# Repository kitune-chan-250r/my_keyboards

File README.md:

# my_keyboards

## первый
・34key,ortholinear,ISO Enter

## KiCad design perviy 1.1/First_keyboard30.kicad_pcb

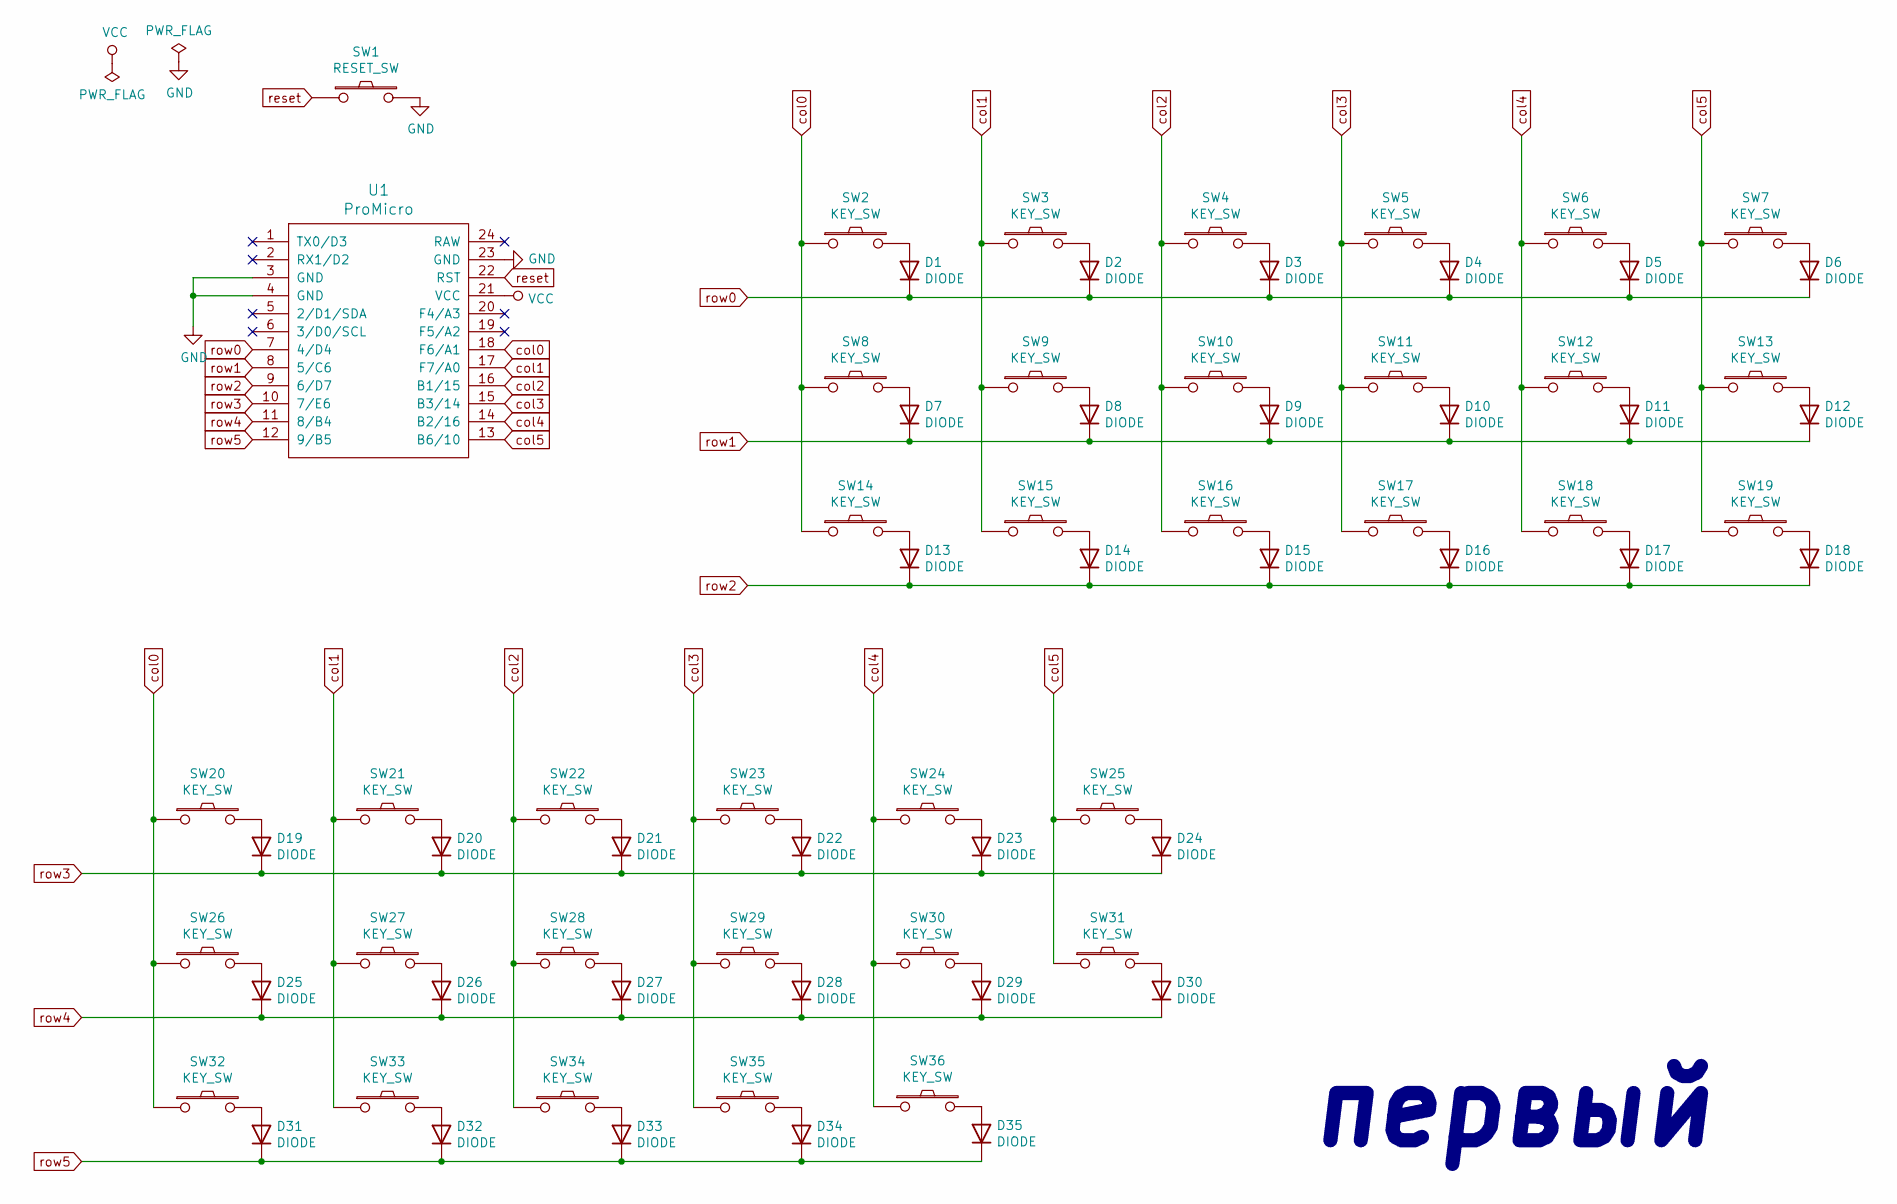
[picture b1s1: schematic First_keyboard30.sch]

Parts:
D1, D2, D3, D4, D5, D6, D7, D8, D9, D10, D11, D12, D13, D14, D15, D16, D17, D18, D19, D20, D21, D22, D23, D24, D25, D26, D27, D28, D29, D30, D31, D32, D33, D34, D35: DIODE; D3_TH_SMD
SW1: RESET_SW; ResetSW
SW2, SW3, SW4, SW5, SW6, SW7, SW8, SW9, SW10, SW11, SW12, SW13, SW16, SW17, SW18, SW19, SW20, SW21, SW22, SW23, SW24, SW25, SW26, SW27, SW28, SW29, SW30, SW31, SW32, SW33, SW34, SW35: KEY_SW; CherryMX_Hotswap
SW14, SW15: KEY_SW; CherryMX_1u
SW36: KEY_SW; MX-Alps-Choc-2U
U1: ProMicro; ProMicro_v3

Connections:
GND: SW1.2, U1.3 (GND), U1.4 (GND), U1.23 (GND)
unnamed: D1.1 (A), SW2.2
unnamed: D2.1 (A), SW3.2
unnamed: D3.1 (A), SW4.2
unnamed: D4.1 (A), SW5.2
unnamed: D5.1 (A), SW6.2
unnamed: D6.1 (A), SW7.2
unnamed: D7.1 (A), SW8.2
unnamed: D8.1 (A), SW9.2
unnamed: D9.1 (A), SW10.2
unnamed: D10.1 (A), SW11.2
unnamed: D11.1 (A), SW12.2
unnamed: D12.1 (A), SW13.2
unnamed: D13.1 (A), SW14.2
unnamed: D14.1 (A), SW15.2
unnamed: D15.1 (A), SW16.2
unnamed: D16.1 (A), SW17.2
unnamed: D17.1 (A), SW18.2
unnamed: D18.1 (A), SW19.2
unnamed: D19.1 (A), SW20.2
unnamed: D20.1 (A), SW21.2
unnamed: D21.1 (A), SW22.2
unnamed: D22.1 (A), SW23.2
unnamed: D23.1 (A), SW24.2
unnamed: D24.1 (A), SW25.2
unnamed: D25.1 (A), SW26.2
unnamed: D26.1 (A), SW27.2
unnamed: D27.1 (A), SW28.2
unnamed: D28.1 (A), SW29.2
unnamed: D29.1 (A), SW30.2
unnamed: D30.1 (A), SW31.2
unnamed: D31.1 (A), SW32.2
unnamed: D32.1 (A), SW33.2
unnamed: D33.1 (A), SW34.2
unnamed: D34.1 (A), SW35.2
unnamed: D35.1 (A), SW36.2
VCC: U1.21 (VCC)
col0: SW2.1, SW8.1, SW14.1, SW20.1, SW26.1, SW32.1, U1.18 (F6/A1)
col1: SW3.1, SW9.1, SW15.1, SW21.1, SW27.1, SW33.1, U1.17 (F7/A0)
col2: SW4.1, SW10.1, SW16.1, SW22.1, SW28.1, SW34.1, U1.16 (B1/15)
col3: SW5.1, SW11.1, SW17.1, SW23.1, SW29.1, SW35.1, U1.15 (B3/14)
col4: SW6.1, SW12.1, SW18.1, SW24.1, SW30.1, SW36.1, U1.14 (B2/16)
col5: SW7.1, SW13.1, SW19.1, SW25.1, SW31.1, U1.13 (B6/10)
reset: SW1.1, U1.22 (RST)
row0: D1.2 (K), D2.2 (K), D3.2 (K), D4.2 (K), D5.2 (K), D6.2 (K), U1.7 (4/D4)
row1: D7.2 (K), D8.2 (K), D9.2 (K), D10.2 (K), D11.2 (K), D12.2 (K), U1.8 (5/C6)
row2: D13.2 (K), D14.2 (K), D15.2 (K), D16.2 (K), D17.2 (K), D18.2 (K), U1.9 (6/D7)
row3: D19.2 (K), D20.2 (K), D21.2 (K), D22.2 (K), D23.2 (K), D24.2 (K), U1.10 (7/E6)
row4: D25.2 (K), D26.2 (K), D27.2 (K), D28.2 (K), D29.2 (K), D30.2 (K), U1.11 (8/B4)
row5: D31.2 (K), D32.2 (K), D33.2 (K), D34.2 (K), D35.2 (K), U1.12 (9/B5)

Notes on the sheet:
первый

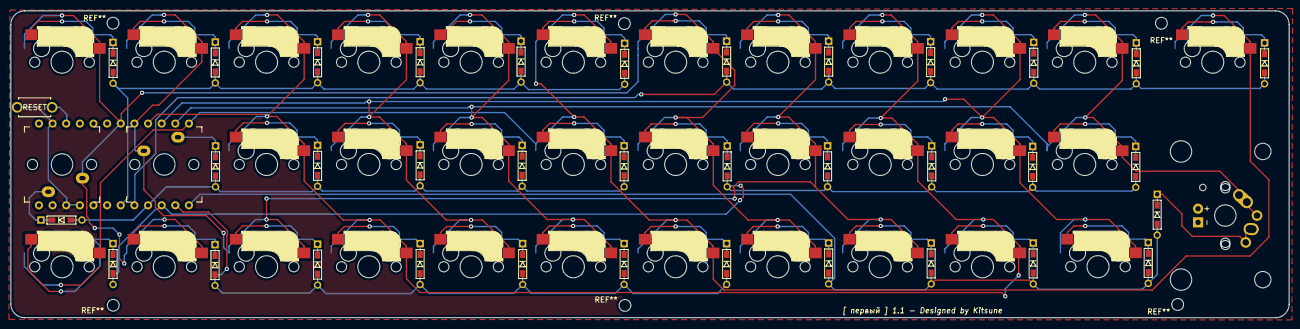
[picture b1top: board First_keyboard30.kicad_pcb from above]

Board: 2 copper layers, 238.1 x 57.2 mm, 72 parts (1 on the bottom side), 49 nets.

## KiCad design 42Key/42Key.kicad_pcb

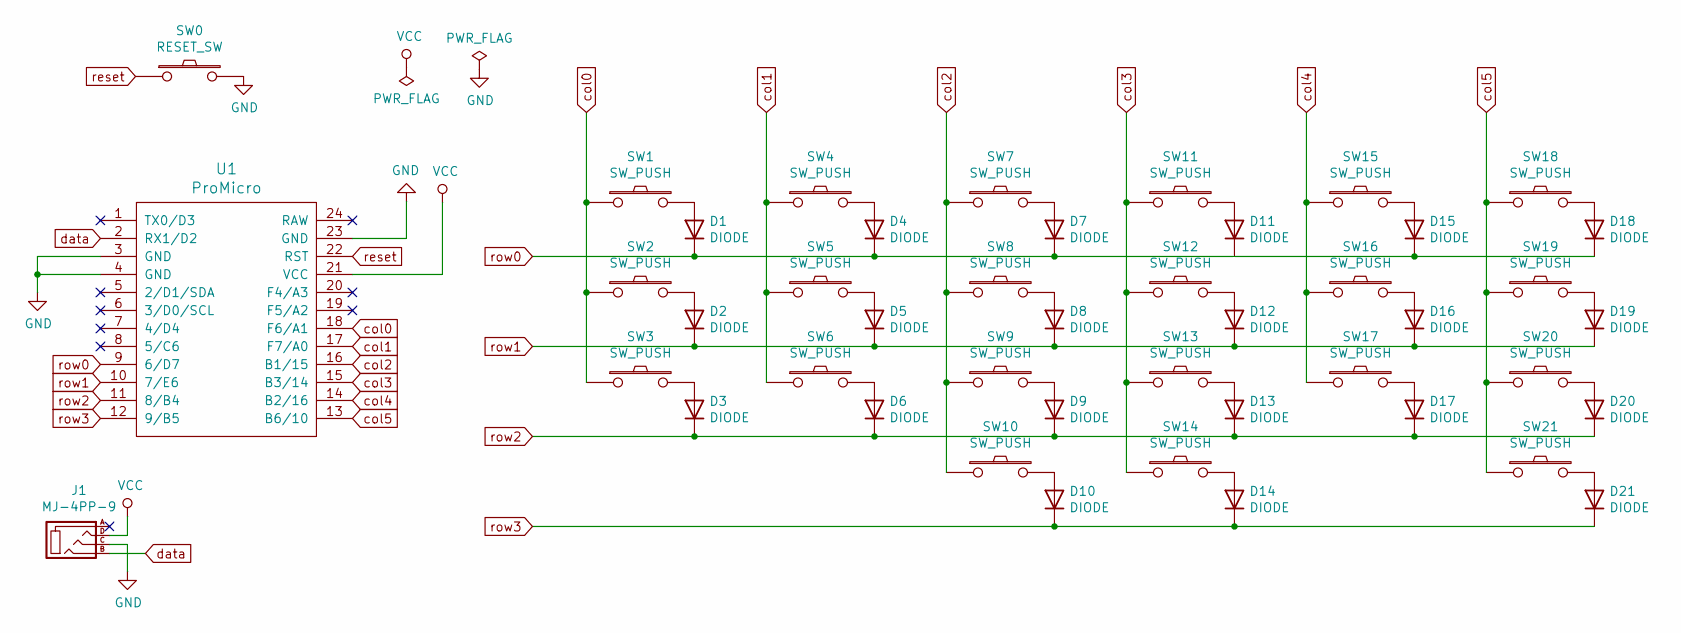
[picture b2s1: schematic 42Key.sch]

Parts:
D1, D2, D3, D4, D5, D6, D7, D8, D9, D10, D11, D12, D13, D14, D15, D16, D17, D18, D19, D20, D21: DIODE; D3_TH_SMD
J1: MJ-4PP-9
SW0: RESET_SW; ResetSW
SW1, SW2, SW3, SW4, SW5, SW6, SW7, SW8, SW9, SW10, SW11, SW12, SW13, SW14, SW15, SW16, SW17, SW18: SW_PUSH; Triple-Dual-1u-LED
SW19, SW20, SW21: SW_PUSH; Triple-Dual-2u-LED
U1: ProMicro; ProMicro_v2

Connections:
GND: J1.C, SW0.2, U1.3 (GND), U1.4 (GND), U1.23 (GND)
unnamed: D1.2 (A), SW1.2
unnamed: D2.2 (A), SW2.2
unnamed: D3.2 (A), SW3.2
unnamed: D4.2 (A), SW4.2
unnamed: D5.2 (A), SW5.2
unnamed: D6.2 (A), SW6.2
unnamed: D7.2 (A), SW7.2
unnamed: D8.2 (A), SW8.2
unnamed: D9.2 (A), SW9.2
unnamed: D10.2 (A), SW10.2
unnamed: D11.1 (K), D15.1 (K), D18.1 (K)
unnamed: D11.2 (A), SW11.2
unnamed: D12.2 (A), SW12.2
unnamed: D13.2 (A), SW13.2
unnamed: D14.2 (A), SW14.2
unnamed: D15.2 (A), SW15.2
unnamed: D16.2 (A), SW16.2
unnamed: D17.2 (A), SW17.2
unnamed: D18.2 (A), SW18.2
unnamed: D19.2 (A), SW19.2
unnamed: D20.2 (A), SW20.2
unnamed: D21.2 (A), SW21.2
VCC: J1.D, U1.21 (VCC)
col0: SW1.1, SW2.1, SW3.1, U1.18 (F6/A1)
col1: SW4.1, SW5.1, SW6.1, U1.17 (F7/A0)
col2: SW7.1, SW8.1, SW9.1, SW10.1, U1.16 (B1/15)
col3: SW11.1, SW12.1, SW13.1, SW14.1, U1.15 (B3/14)
col4: SW15.1, SW16.1, SW17.1, U1.14 (B2/16)
col5: SW18.1, SW19.1, SW20.1, SW21.1, U1.13 (B6/10)
data: J1.B, U1.2 (RX1/D2)
reset: SW0.1, U1.22 (RST)
row0: D1.1 (K), D4.1 (K), D7.1 (K), U1.9 (6/D7)
row1: D2.1 (K), D5.1 (K), D8.1 (K), D12.1 (K), D16.1 (K), D19.1 (K), U1.10 (7/E6)
row2: D3.1 (K), D6.1 (K), D9.1 (K), D13.1 (K), D17.1 (K), D20.1 (K), U1.11 (8/B4)
row3: D10.1 (K), D14.1 (K), D21.1 (K), U1.12 (9/B5)

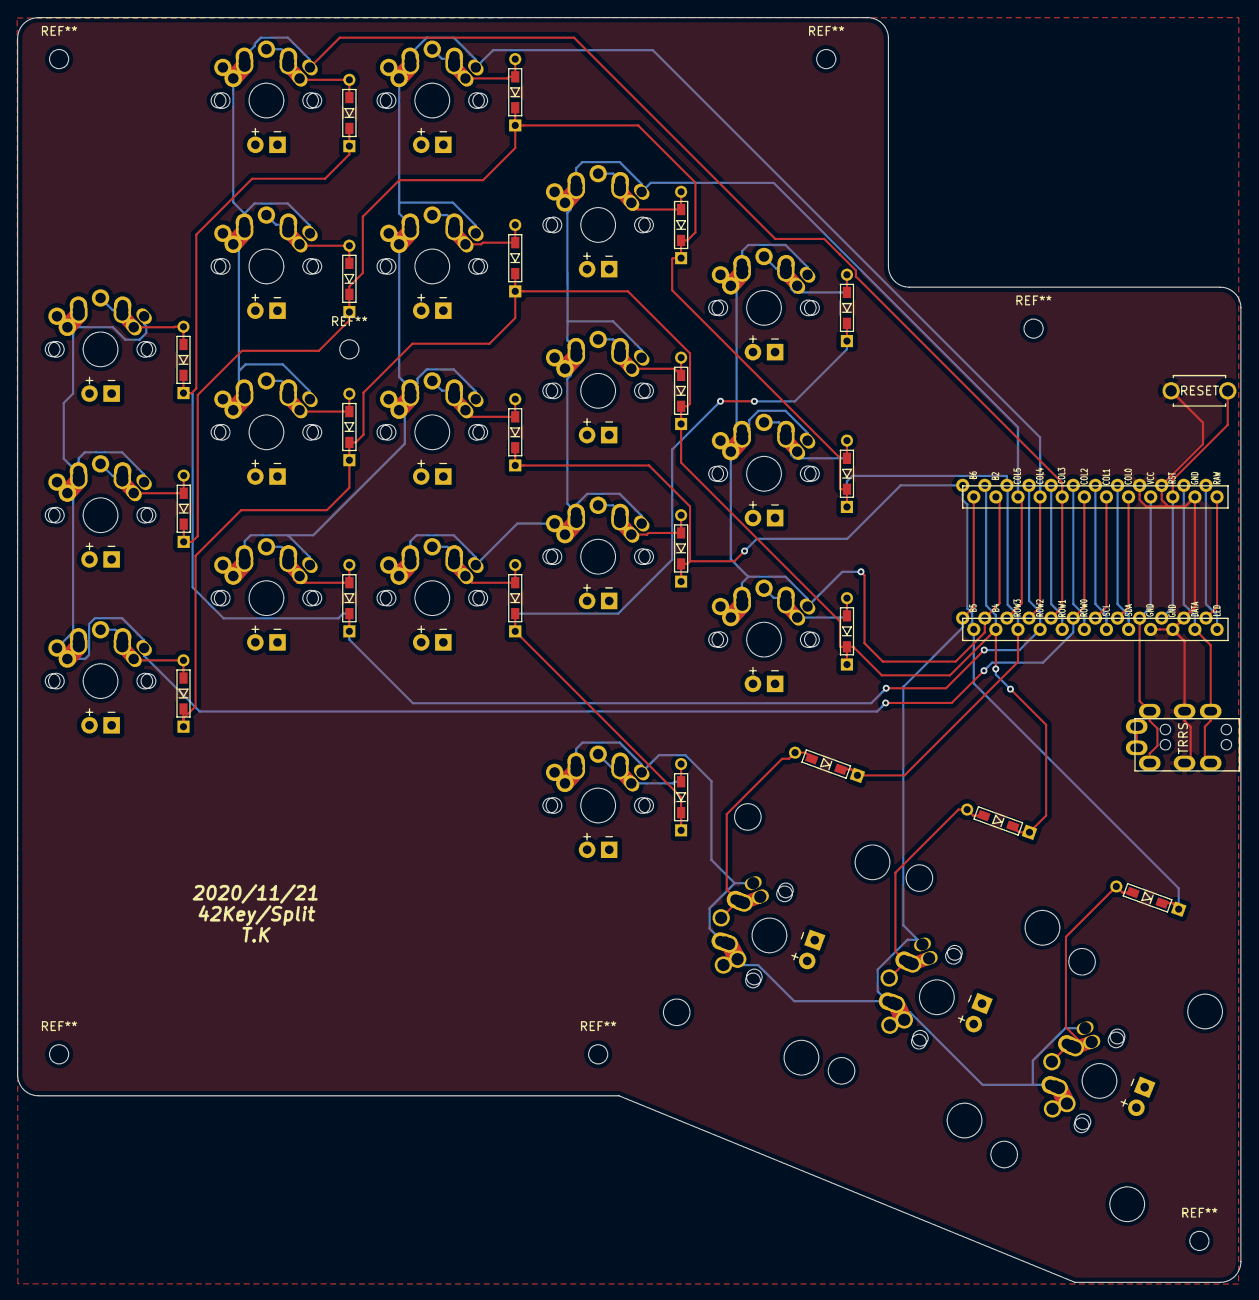
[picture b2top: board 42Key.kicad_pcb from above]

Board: 2 copper layers, 140.5 x 145.3 mm, 45 parts (0 on the bottom side), 36 nets.

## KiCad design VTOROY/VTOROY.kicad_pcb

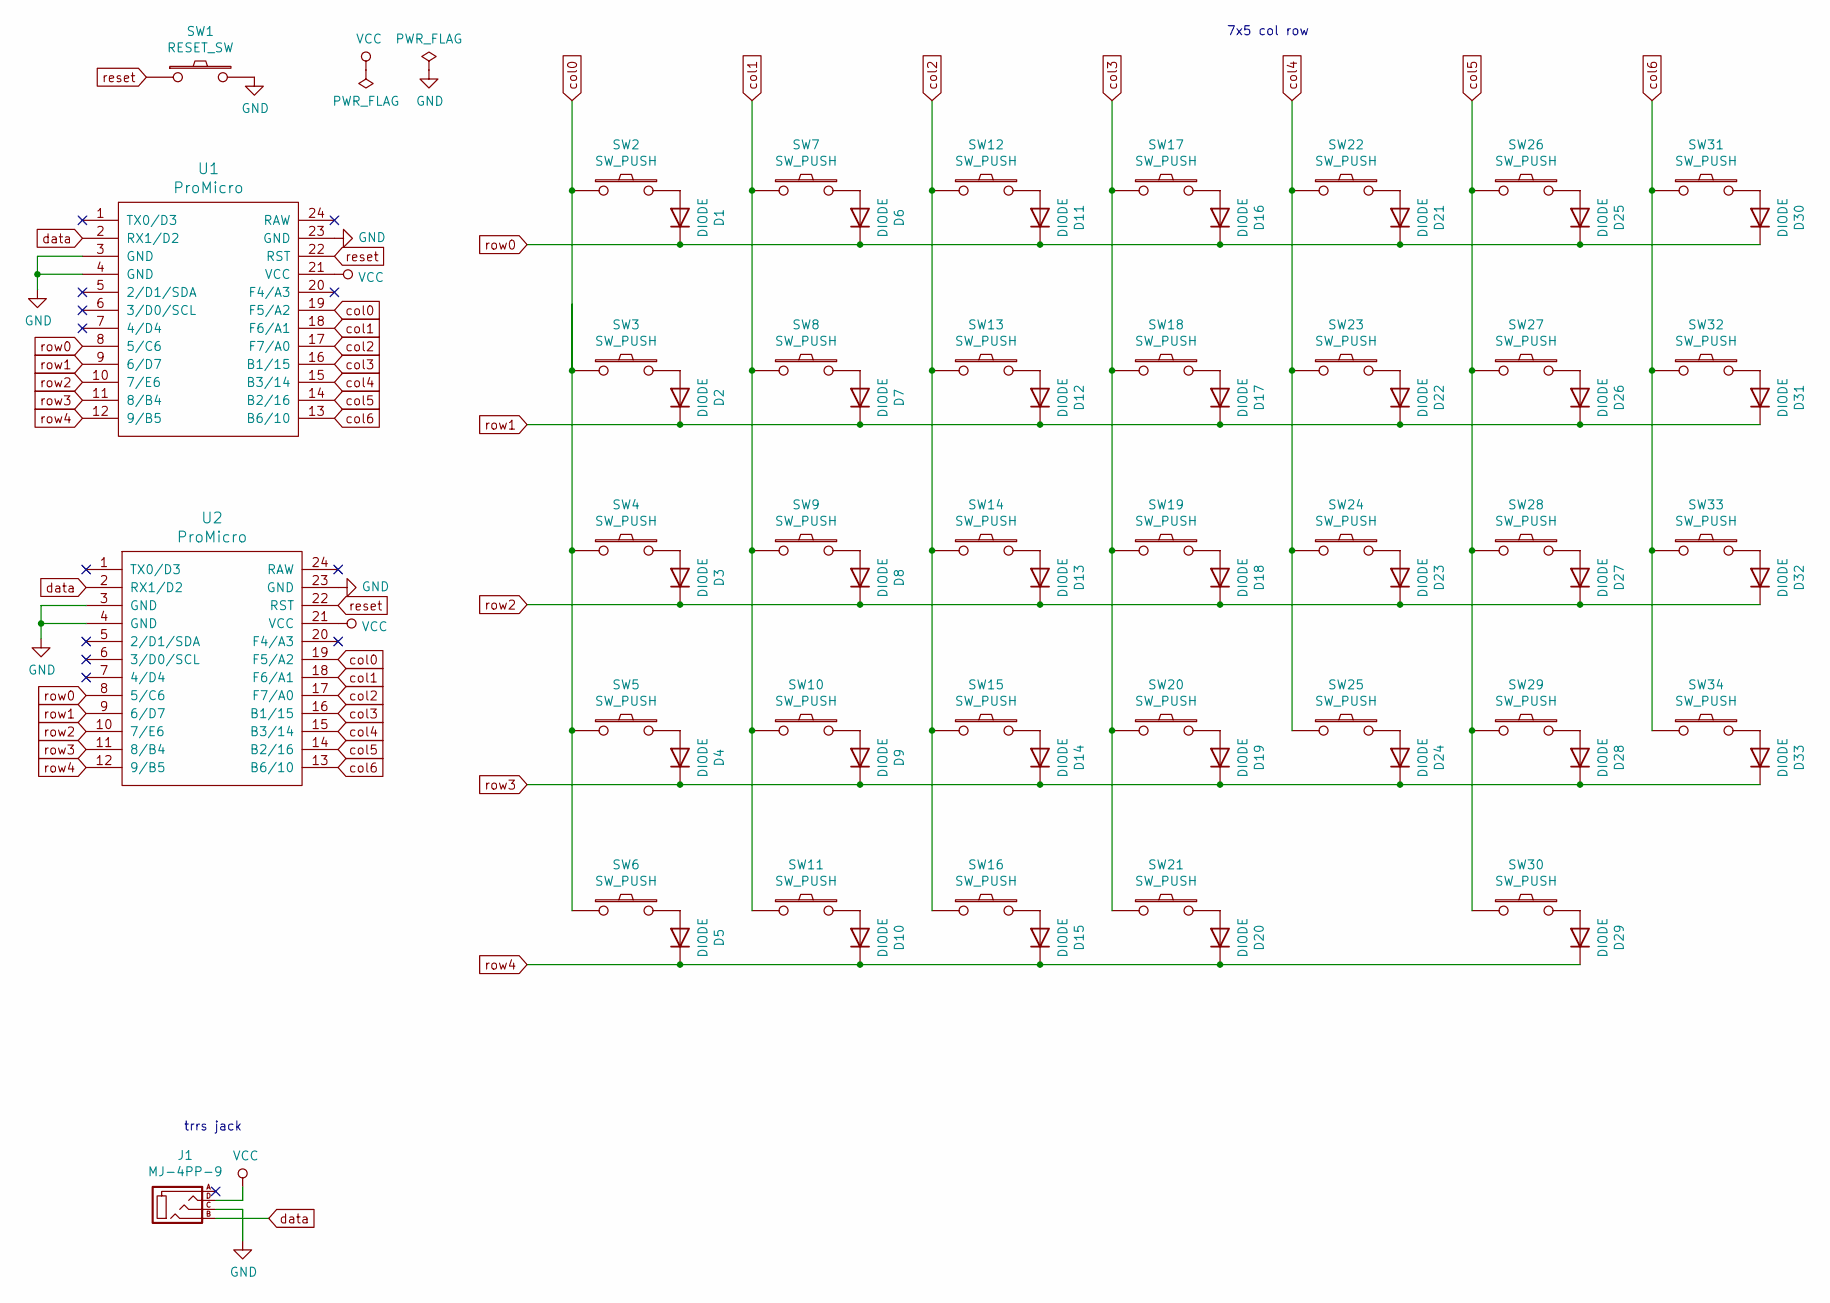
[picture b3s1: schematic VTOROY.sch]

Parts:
D1, D2, D3, D4, D5, D6, D7, D8, D9, D10, D11, D12, D13, D14, D15, D16, D17, D18, D19, D20, D21, D22, D23, D24, D25, D26, D27, D28, D29, D30, D31, D32, D33: DIODE; D3_TH_SMD
J1: MJ-4PP-9; MJ-4PP-9_1side
SW1: RESET_SW; ResetSW
SW2, SW3, SW4, SW5, SW6, SW7, SW8, SW9, SW10, SW11, SW12, SW13, SW14, SW15, SW16, SW17, SW18, SW19, SW20, SW21, SW22, SW23, SW24, SW25, SW26, SW27, SW28, SW29, SW30, SW31, SW32, SW33, SW34: SW_PUSH; SW_MX_reversible
U1, U2: ProMicro; ProMicro_v3

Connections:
GND: J1.C, SW1.2, U1.3 (GND), U1.4 (GND), U1.23 (GND), U2.3 (GND), U2.4 (GND), U2.23 (GND); also elsewhere on the board
unnamed: D1.2 (A), SW2.2
unnamed: D2.2 (A), SW3.2
unnamed: D3.2 (A), SW4.2
unnamed: D4.2 (A), SW5.2
unnamed: D5.2 (A), SW6.2
unnamed: D6.2 (A), SW7.2
unnamed: D7.2 (A), SW8.2
unnamed: D8.2 (A), SW9.2
unnamed: D9.2 (A), SW10.2
unnamed: D10.2 (A), SW11.2
unnamed: D11.2 (A), SW12.2
unnamed: D12.2 (A), SW13.2
unnamed: D13.2 (A), SW14.2
unnamed: D14.2 (A), SW15.2
unnamed: D15.2 (A), SW16.2
unnamed: D16.2 (A), SW17.2
unnamed: D17.2 (A), SW18.2
unnamed: D18.2 (A), SW19.2
unnamed: D19.2 (A), SW20.2
unnamed: D20.2 (A), SW21.2
unnamed: D21.2 (A), SW22.2
unnamed: D22.2 (A), SW23.2
unnamed: D23.2 (A), SW24.2
unnamed: D24.2 (A), SW25.2
unnamed: D25.2 (A), SW26.2
unnamed: D26.2 (A), SW27.2
unnamed: D27.2 (A), SW28.2
unnamed: D28.2 (A), SW29.2
unnamed: D29.2 (A), SW30.2
unnamed: D30.2 (A), SW31.2
unnamed: D31.2 (A), SW32.2
unnamed: D32.2 (A), SW33.2
unnamed: D33.2 (A), SW34.2
unnamed 34: J1.A; also elsewhere on the board
VCC: J1.D, U1.21 (VCC), U2.21 (VCC); also elsewhere on the board
col0: SW2.1, SW3.1, SW4.1, SW5.1, SW6.1, U1.19 (F5/A2), U2.19 (F5/A2)
col1: SW7.1, SW8.1, SW9.1, SW10.1, SW11.1, U1.18 (F6/A1), U2.18 (F6/A1)
col2: SW12.1, SW13.1, SW14.1, SW15.1, SW16.1, U1.17 (F7/A0), U2.17 (F7/A0)
col3: SW17.1, SW18.1, SW19.1, SW20.1, SW21.1, U1.16 (B1/15), U2.16 (B1/15)
col4: SW22.1, SW23.1, SW24.1, SW25.1, U1.15 (B3/14), U2.15 (B3/14)
col5: SW26.1, SW27.1, SW28.1, SW29.1, SW30.1, U1.14 (B2/16), U2.14 (B2/16)
col6: SW31.1, SW32.1, SW33.1, SW34.1, U1.13 (B6/10), U2.13 (B6/10)
data: J1.B, U1.2 (RX1/D2), U2.2 (RX1/D2); also elsewhere on the board
reset: SW1.1, U1.22 (RST), U2.22 (RST)
row0: D1.1 (K), D6.1 (K), D11.1 (K), D16.1 (K), D21.1 (K), D25.1 (K), D30.1 (K), U1.8 (5/C6), U2.8 (5/C6)
row1: D2.1 (K), D7.1 (K), D12.1 (K), D17.1 (K), D22.1 (K), D26.1 (K), D31.1 (K), U1.9 (6/D7), U2.9 (6/D7)
row2: D3.1 (K), D8.1 (K), D13.1 (K), D18.1 (K), D23.1 (K), D27.1 (K), D32.1 (K), U1.10 (7/E6), U2.10 (7/E6)
row3: D4.1 (K), D9.1 (K), D14.1 (K), D19.1 (K), D24.1 (K), D28.1 (K), D33.1 (K), U1.11 (8/B4), U2.11 (8/B4)
row4: D5.1 (K), D10.1 (K), D15.1 (K), D20.1 (K), D29.1 (K), U1.12 (9/B5), U2.12 (9/B5)

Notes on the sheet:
trrs jack
7x5 col row

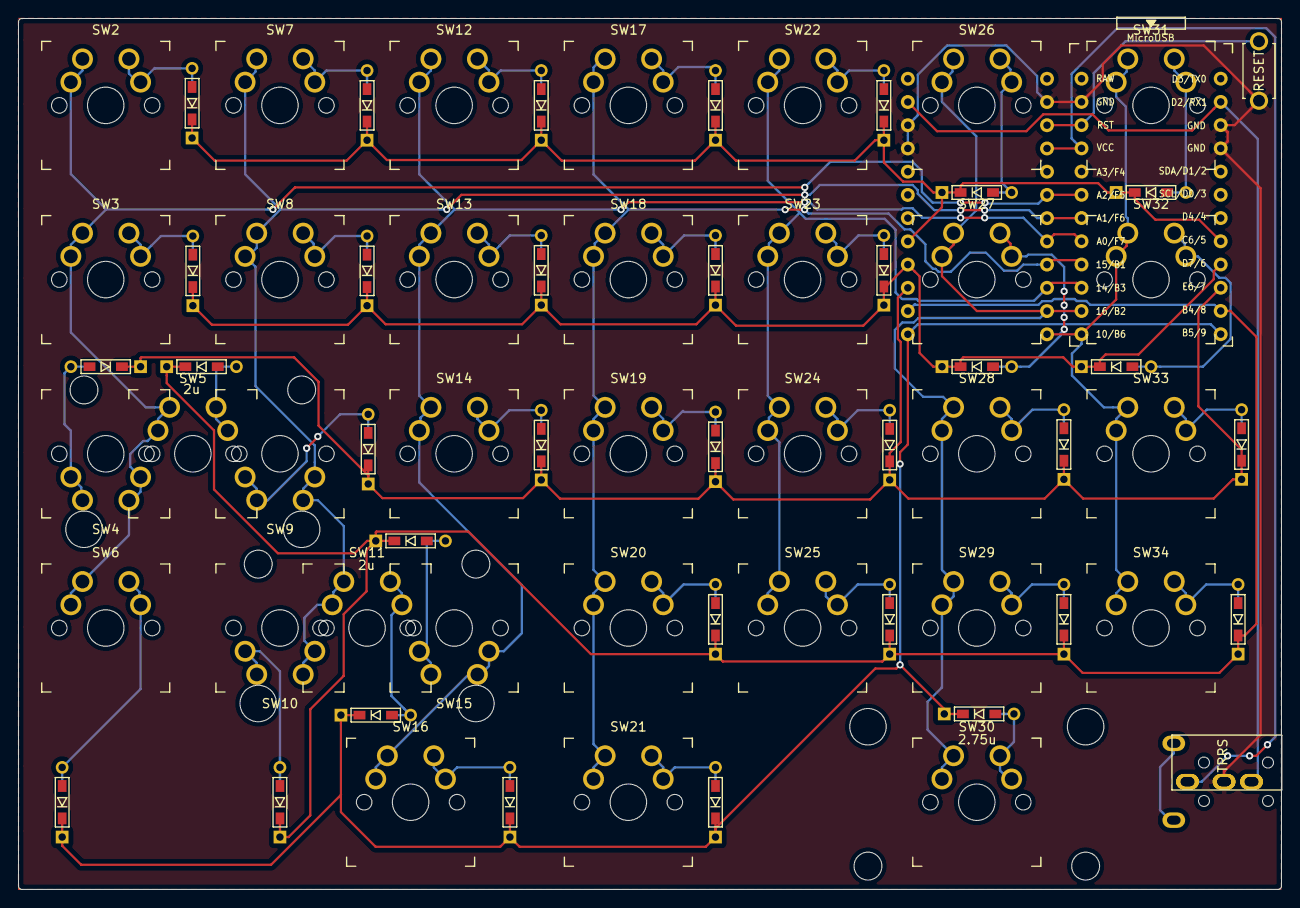
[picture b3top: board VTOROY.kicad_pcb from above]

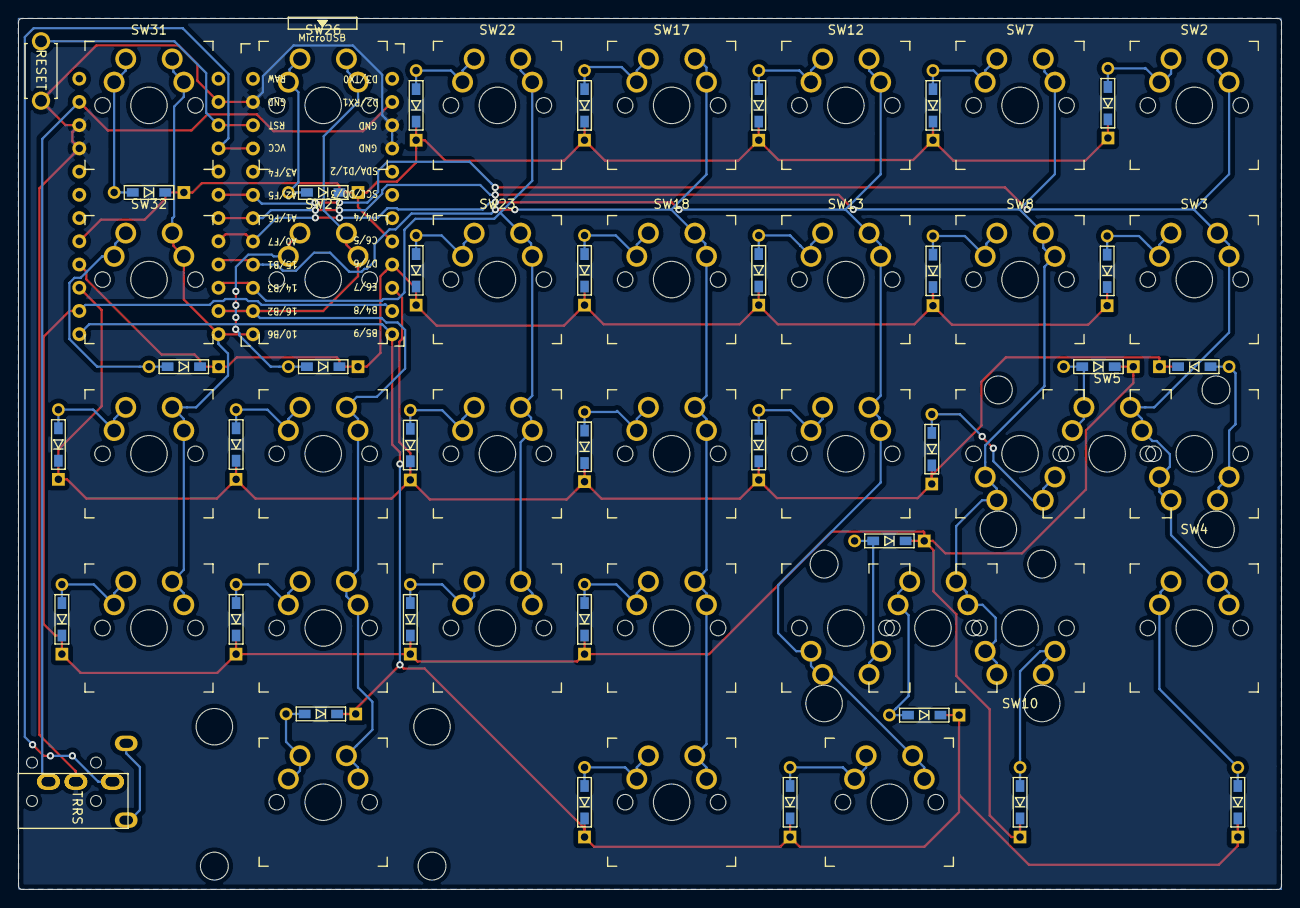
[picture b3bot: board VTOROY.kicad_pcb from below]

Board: 2 copper layers, 138.1 x 95.2 mm, 71 parts (2 on the bottom side), 50 nets.

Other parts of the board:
J1#2: MJ-4PP-9; MJ-4PP-9_1side

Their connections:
GND: J1#2.C; also elsewhere on the board
unnamed 34: J1#2.A; also elsewhere on the board
VCC: J1#2.D; also elsewhere on the board
data: J1#2.B; also elsewhere on the board

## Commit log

2019-12-19 初自作キーボードを追加
2019-12-19 add .dfx
2019-12-19 circuit diagram compleat
2019-12-19 pcb update
2019-12-19 Update fp-info-cache
2019-12-20 update pcb
2019-12-20 GND mask
2019-12-20 draw dxf
2019-12-21 add test firmware
2019-12-21 add logo
2019-12-21 rename
2019-12-23 fix pcb
2019-12-23 plate
2019-12-24 new keyboard
2019-12-25 save
2019-12-25 new file and new dir
    add .gitignore
    add dir "completion file"
2019-12-29 add Gerber file
2020-01-16 プレート同士のずれを修正
2020-02-27 perviy 1.1
2020-02-27 add gb file
2020-11-21 compleate
2021-01-12 new keyboard
    Маленький
    4Key mini macropad
2021-01-12 aouto save
